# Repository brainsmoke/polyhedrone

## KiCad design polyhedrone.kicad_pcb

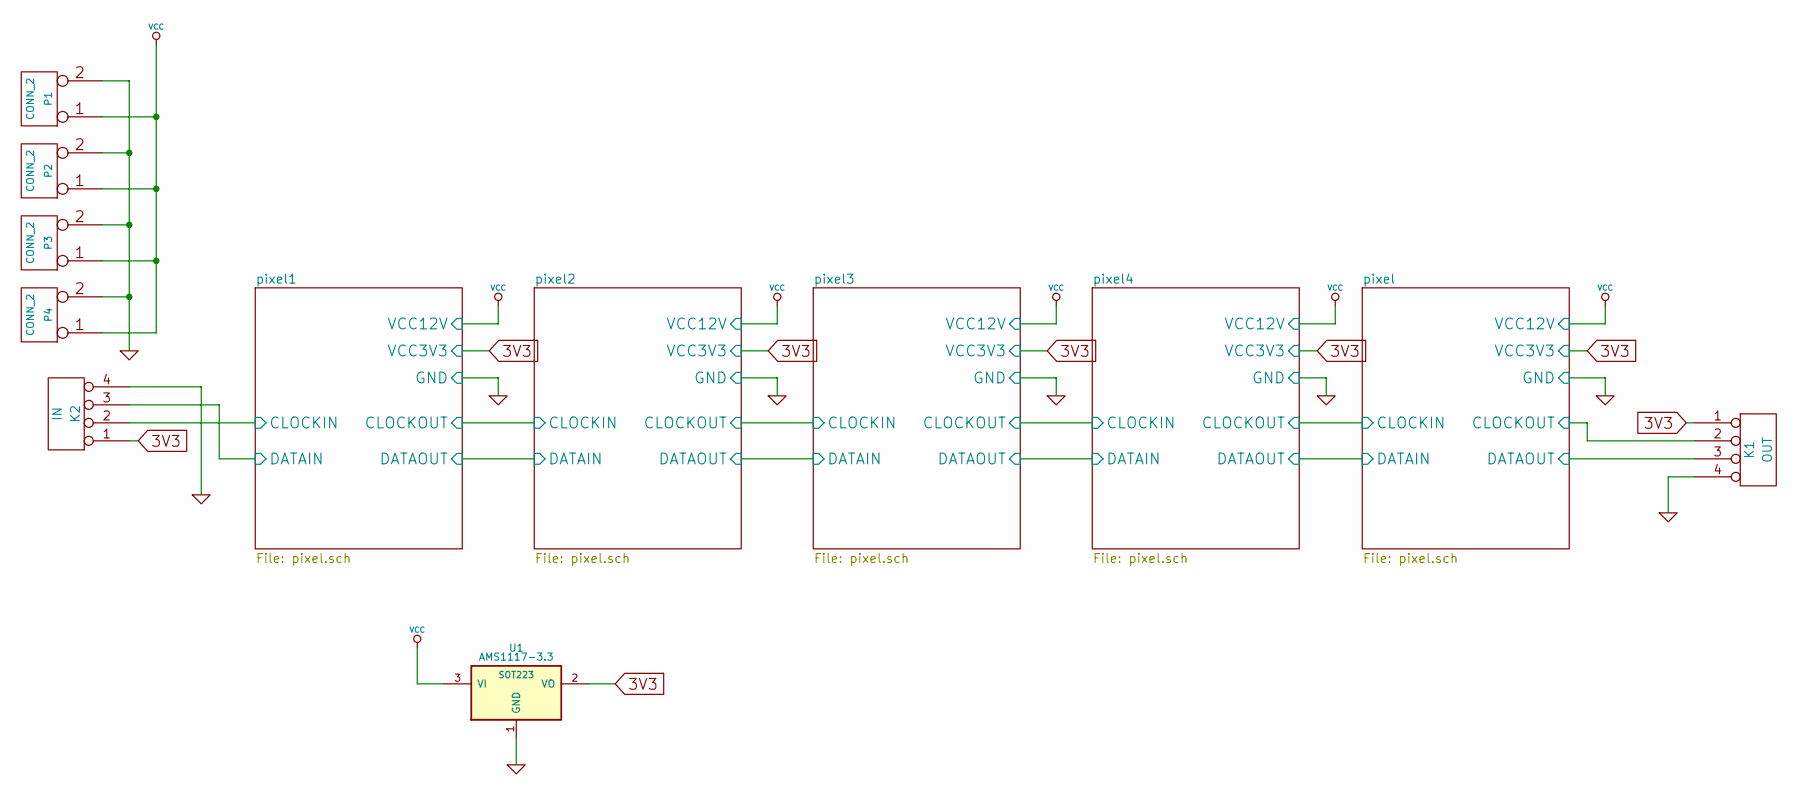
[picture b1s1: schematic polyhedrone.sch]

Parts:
K1: OUT
K2: IN
P1, P2, P3, P4: CONN_2
U1: AMS1117-3.3; SOT223

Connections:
3V3: K1.1, K2.1, U1.2 (VO); also elsewhere on the board
/pixel1/CLOCKIN: K2.2; also elsewhere on the board
/pixel1/DATAIN: K2.3; also elsewhere on the board
/pixel/CLOCKOUT: K1.2; also elsewhere on the board
/pixel/DATAOUT: K1.3; also elsewhere on the board
GND: K1.4, K2.4, P1.2 (PM), P2.2 (PM), P3.2 (PM), P4.2 (PM), U1.1 (GND); also elsewhere on the board
VCC: P1.1, P2.1, P3.1, P4.1, U1.3 (VI); also elsewhere on the board

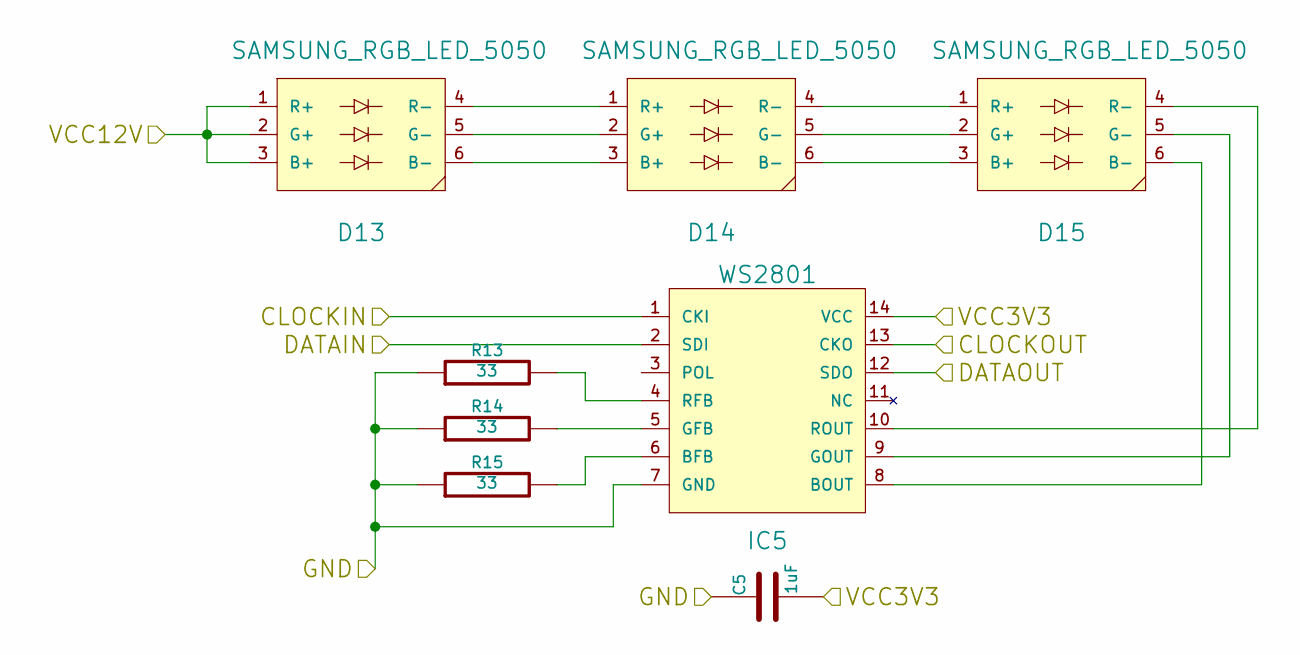
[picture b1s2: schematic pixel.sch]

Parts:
C1: 1uF
D1, D2, D3: SAMSUNG_RGB_LED_5050
IC1: WS2801
R1, R2, R3: 33

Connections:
3V3: C1.2, IC1.14 (VCC); also elsewhere on the board
/pixel1/CLOCKIN: IC1.1 (CKI); also elsewhere on the board
/pixel1/DATAIN: IC1.2 (SDI); also elsewhere on the board
/pixel2/CLOCKIN: IC1.13 (CKO); also elsewhere on the board
/pixel2/DATAIN: IC1.12 (SDO); also elsewhere on the board
GND: C1.1, IC1.7 (GND), R1.1, R2.1, R3.1; also elsewhere on the board
unnamed: IC1.6 (BFB), R3.2
unnamed: IC1.4 (RFB), R1.2
unnamed: IC1.5 (GFB), R2.2
unnamed: D3.6 (B-), IC1.8 (BOUT)
unnamed: D3.4 (R-), IC1.10 (ROUT)
unnamed: D3.5 (G-), IC1.9 (GOUT)
unnamed: D2.4 (R-), D3.1 (R+)
unnamed: D2.6 (B-), D3.3 (B+)
unnamed: D2.5 (G-), D3.2 (G+)
unnamed: D1.6 (B-), D2.3 (B+)
unnamed: D1.5 (G-), D2.2 (G+)
unnamed: D1.4 (R-), D2.1 (R+)
VCC: D1.1 (R+), D1.2 (G+), D1.3 (B+); also elsewhere on the board

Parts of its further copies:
C2, C3, C4, C5: 1uF
D4, D5, D6, D7, D8, D9, D10, D11, D12, D13, D14, D15: SAMSUNG_RGB_LED_5050
IC2, IC3, IC4, IC5: WS2801
R4, R5, R6, R7, R8, R9, R10, R11, R12, R13, R14, R15: 33

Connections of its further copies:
3V3: C2.2, C3.2, C4.2, C5.2, IC2.14 (VCC), IC3.14 (VCC), IC4.14 (VCC), IC5.14 (VCC); also elsewhere on the board
/pixel2/CLOCKIN: IC2.1 (CKI); also elsewhere on the board
/pixel2/DATAIN: IC2.2 (SDI); also elsewhere on the board
/pixel3/CLOCKIN: IC2.13 (CKO), IC3.1 (CKI)
/pixel3/DATAIN: IC2.12 (SDO), IC3.2 (SDI)
/pixel4/CLOCKIN: IC3.13 (CKO), IC4.1 (CKI)
/pixel4/DATAIN: IC3.12 (SDO), IC4.2 (SDI)
/pixel/CLOCKIN: IC4.13 (CKO), IC5.1 (CKI)
/pixel/CLOCKOUT: IC5.13 (CKO); also elsewhere on the board
/pixel/DATAIN: IC4.12 (SDO), IC5.2 (SDI)
/pixel/DATAOUT: IC5.12 (SDO); also elsewhere on the board
GND: C2.1, C3.1, C4.1, C5.1, IC2.7 (GND), IC3.7 (GND), IC4.7 (GND), IC5.7 (GND), R4.1, R5.1, R6.1, R7.1, R8.1, R9.1, R10.1, R11.1, R12.1, R13.1, R14.1, R15.1; also elsewhere on the board
unnamed: IC2.6 (BFB), R6.2
unnamed: IC2.4 (RFB), R4.2
unnamed: IC2.5 (GFB), R5.2
unnamed: D6.6 (B-), IC2.8 (BOUT)
unnamed: D6.4 (R-), IC2.10 (ROUT)
unnamed: D6.5 (G-), IC2.9 (GOUT)
unnamed: D5.5 (G-), D6.2 (G+)
unnamed: D5.6 (B-), D6.3 (B+)
unnamed: D5.4 (R-), D6.1 (R+)
unnamed: D4.6 (B-), D5.3 (B+)
unnamed: D4.5 (G-), D5.2 (G+)
unnamed: D4.4 (R-), D5.1 (R+)
unnamed: IC3.6 (BFB), R9.2
unnamed: IC3.4 (RFB), R7.2
unnamed: IC3.5 (GFB), R8.2
unnamed: D8.6 (B-), D9.3 (B+)
unnamed: D9.4 (R-), IC3.10 (ROUT)
unnamed: D9.5 (G-), IC3.9 (GOUT)
unnamed: D9.6 (B-), IC3.8 (BOUT)
unnamed: D8.5 (G-), D9.2 (G+)
unnamed: D8.4 (R-), D9.1 (R+)
unnamed: D7.6 (B-), D8.3 (B+)
unnamed: D7.5 (G-), D8.2 (G+)
unnamed: D7.4 (R-), D8.1 (R+)
unnamed: IC4.6 (BFB), R12.2
unnamed: IC4.4 (RFB), R10.2
unnamed: IC4.5 (GFB), R11.2
unnamed: D12.6 (B-), IC4.8 (BOUT)
unnamed: D12.4 (R-), IC4.10 (ROUT)
unnamed: D12.5 (G-), IC4.9 (GOUT)
unnamed: D11.4 (R-), D12.1 (R+)
unnamed: D11.6 (B-), D12.3 (B+)
unnamed: D11.5 (G-), D12.2 (G+)
unnamed: D10.6 (B-), D11.3 (B+)
unnamed: D10.5 (G-), D11.2 (G+)
unnamed: D10.4 (R-), D11.1 (R+)
unnamed: IC5.6 (BFB), R15.2
unnamed: IC5.4 (RFB), R13.2
unnamed: IC5.5 (GFB), R14.2
unnamed: D15.6 (B-), IC5.8 (BOUT)
unnamed: D15.4 (R-), IC5.10 (ROUT)
unnamed: D15.5 (G-), IC5.9 (GOUT)
unnamed: D14.5 (G-), D15.2 (G+)
unnamed: D14.6 (B-), D15.3 (B+)
unnamed: D14.4 (R-), D15.1 (R+)
unnamed: D13.6 (B-), D14.3 (B+)
unnamed: D13.5 (G-), D14.2 (G+)
unnamed: D13.4 (R-), D14.1 (R+)
VCC: D4.1 (R+), D4.2 (G+), D4.3 (B+), D7.1 (R+), D7.2 (G+), D7.3 (B+), D10.1 (R+), D10.2 (G+), D10.3 (B+), D13.1 (R+), D13.2 (G+), D13.3 (B+); also elsewhere on the board

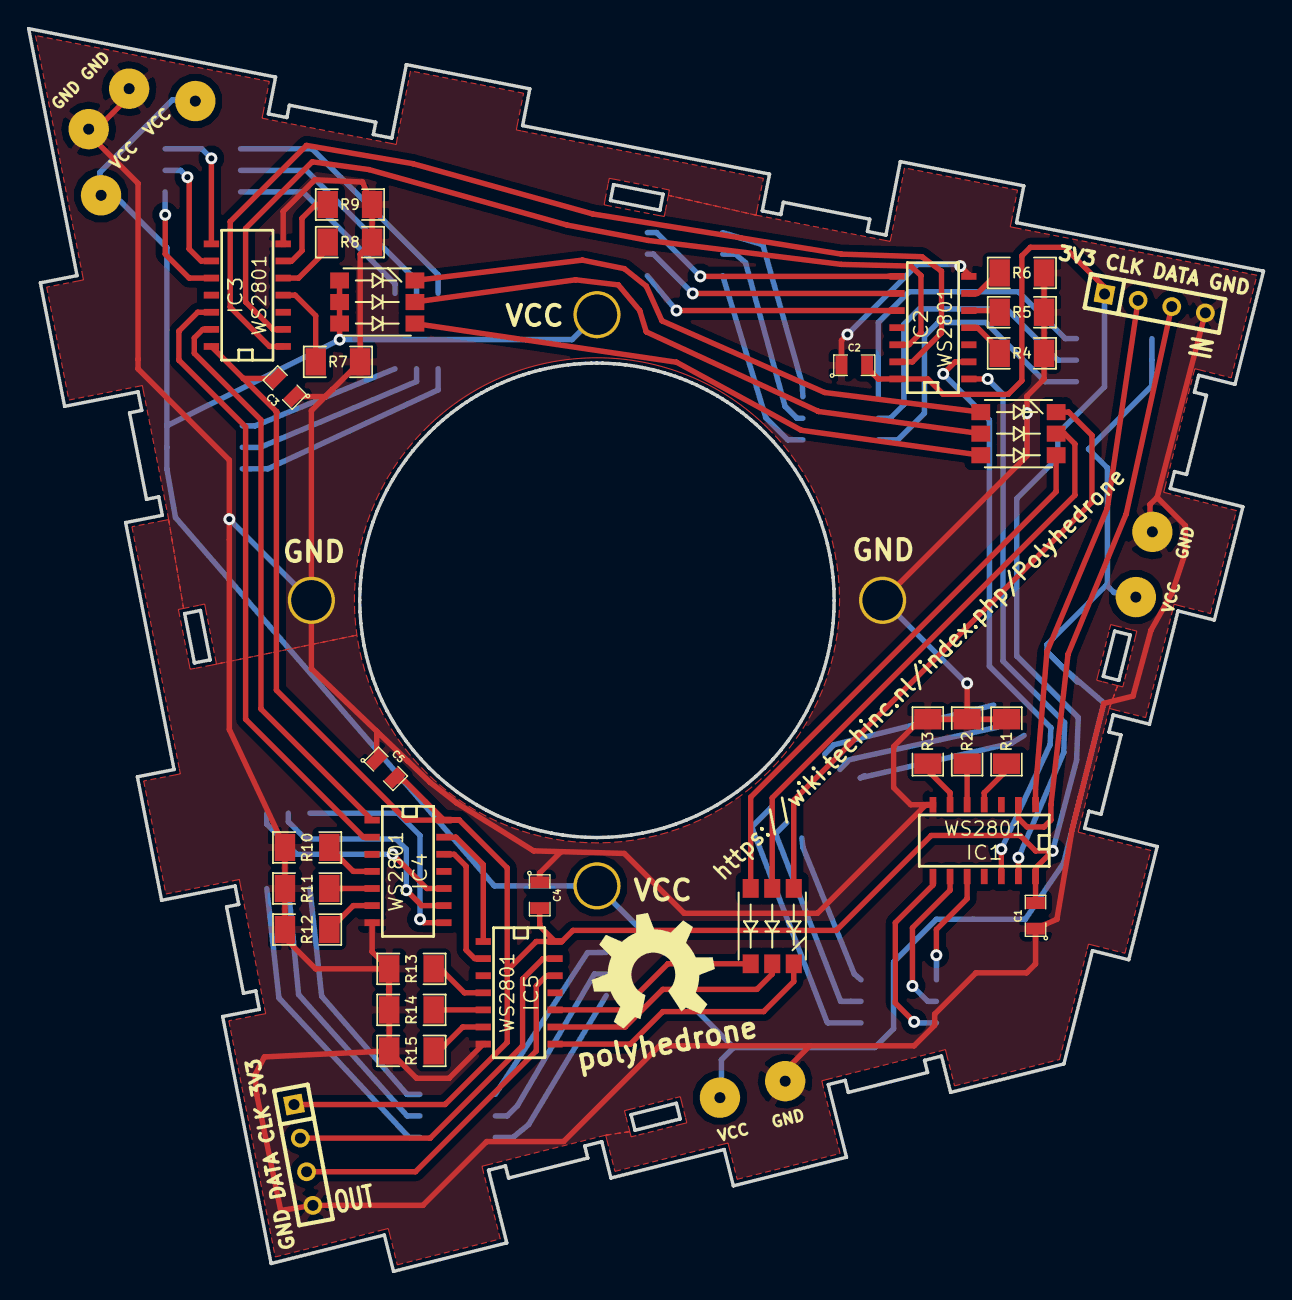
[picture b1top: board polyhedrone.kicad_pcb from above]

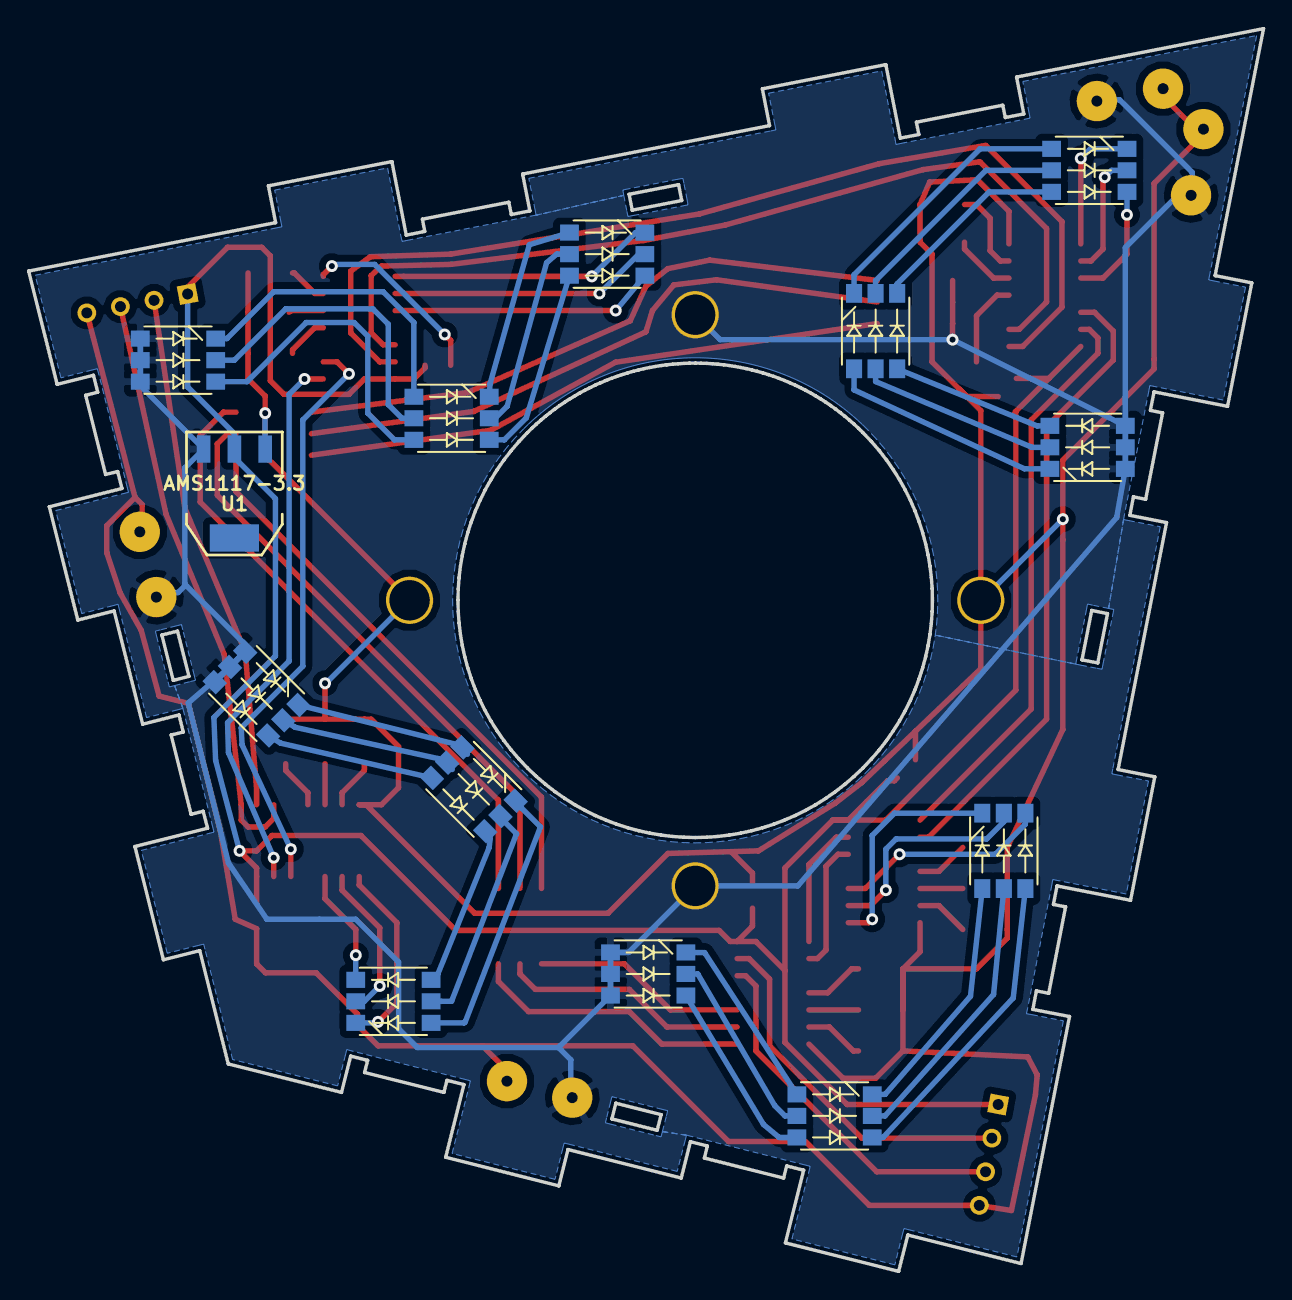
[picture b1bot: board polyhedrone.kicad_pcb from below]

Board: 2 copper layers, 91.7 x 92.3 mm, 47 parts (13 on the bottom side), 75 nets.

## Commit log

2014-06-22 should have done this a while ago
2014-07-25 locking pcb shape
